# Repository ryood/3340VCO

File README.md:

# 3340VCO

AS3340/CEM3340を使用したアナログVCOです。

## 機能概要

電源入力 ±12V (Eurorack電源 10Pin)

### コントロール
FINE:  -0.5オクターブ～+0.5オクターブ連続可変

OCTAVE:  +0オクターブ～+4オクターブ切り替え

MOD:  モジュレーション・レベル

PWM:  PWMレベル調整 (PULSE_WIDTH設定値～PWM入力)

PULSE_WIDTH:  パルス幅調整

### 入出力
CV_IN:  CV入力

MOD_IN:  モジュレーション入力

PWM_IN:  PWM入力

OUT:  音声出力

入力信号電圧: -5V～+5V　出力信号振幅: -4V～+4V 

## 参考記事
[音源とオーディオの電子工作（予定）：3340VCO](https://dad8893.blogspot.com/search/label/3340VCO)

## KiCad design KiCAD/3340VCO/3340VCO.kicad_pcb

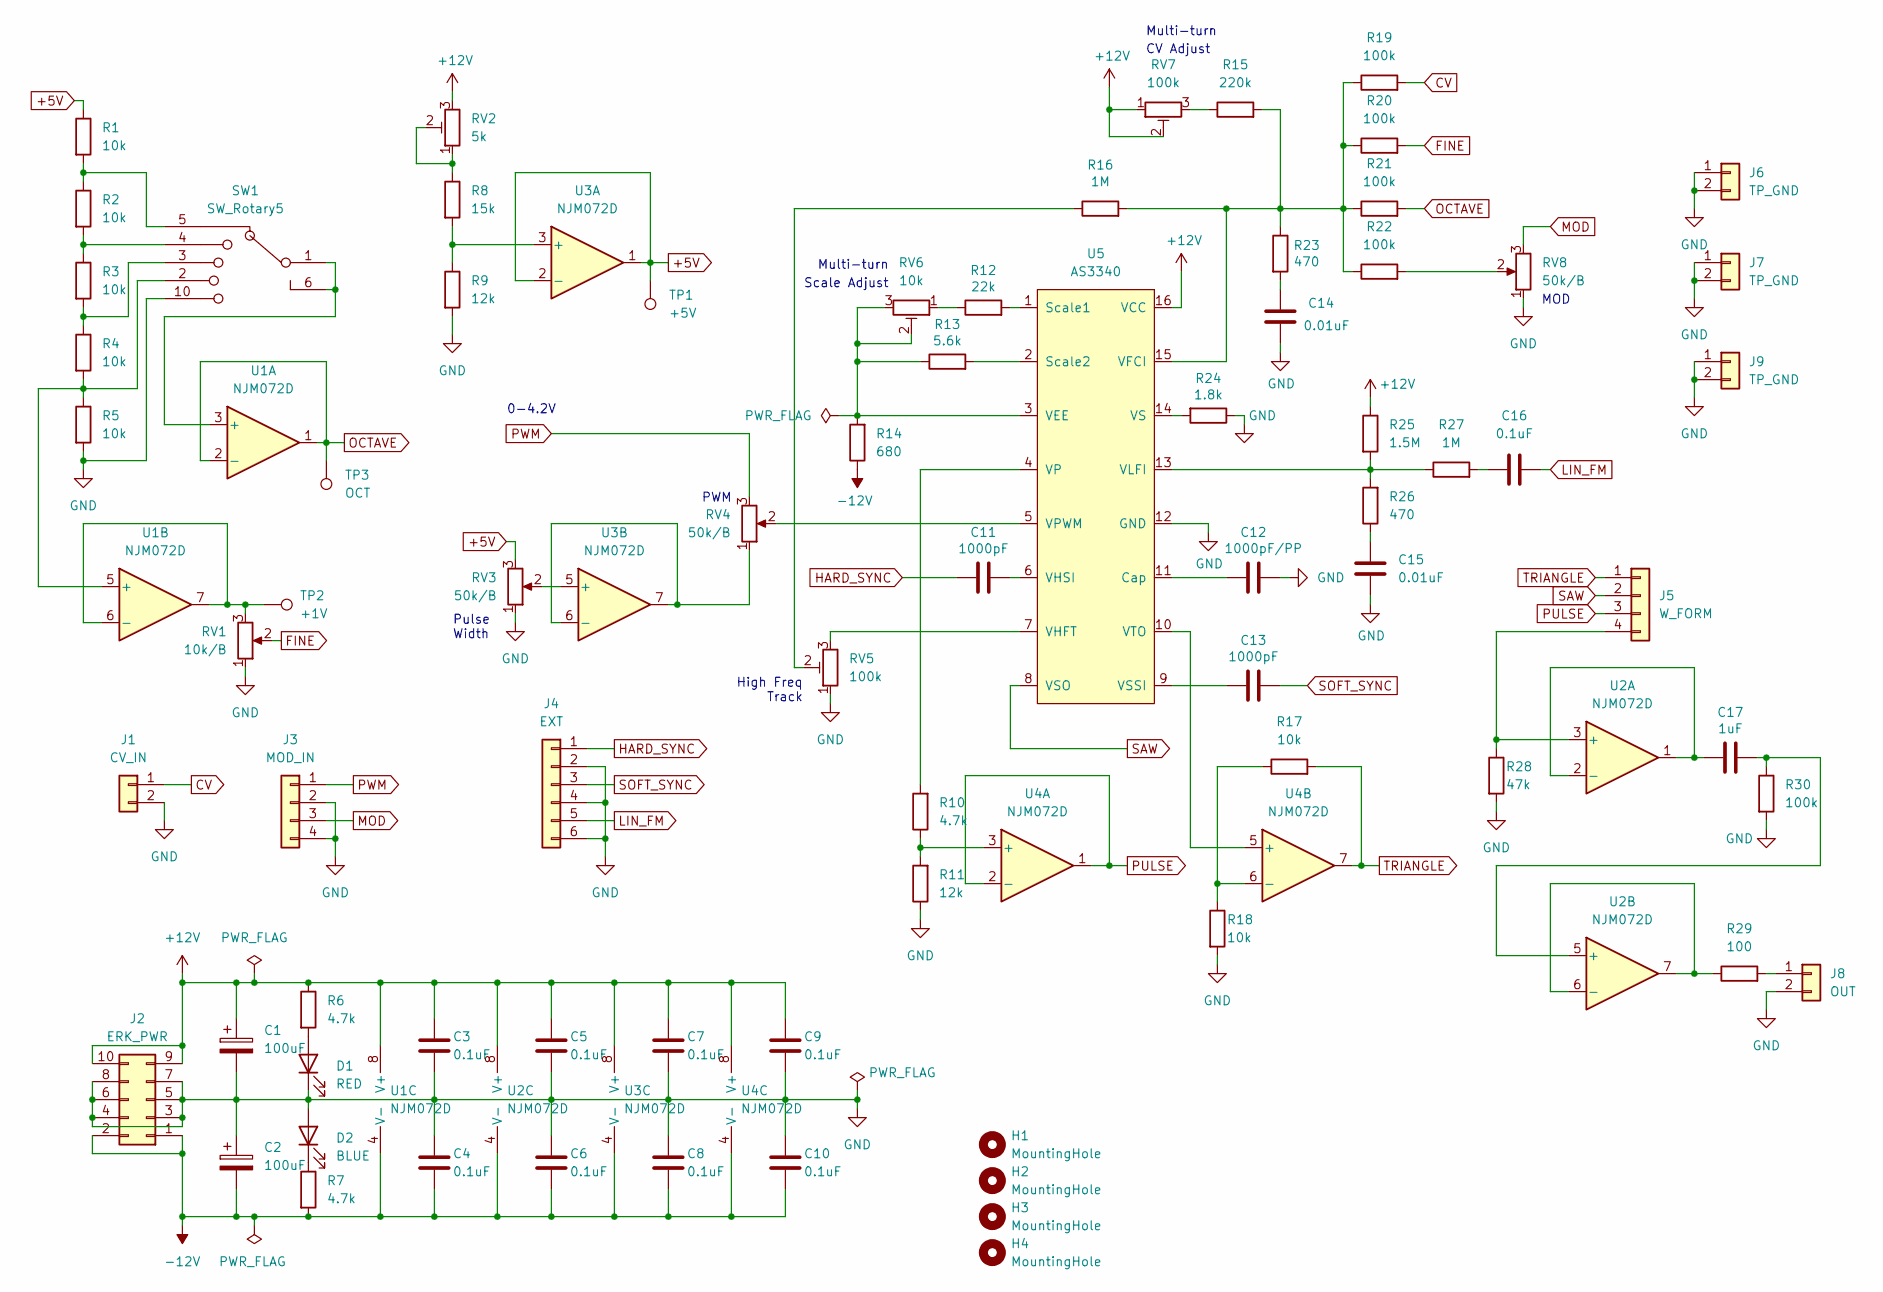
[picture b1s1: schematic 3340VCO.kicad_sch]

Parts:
C1, C2: 100uF; CP_Radial_D6.3mm_P2.50mm
C3, C4, C5, C6, C7, C8, C9, C10: 0.1uF; C_Disc_D3.0mm_W1.6mm_P2.50mm
C11, C13: 1000pF; C_Rect_L7.0mm_W2.0mm_P5.00mm
C12: 1000pF/PP; C_Rect_L7.0mm_W2.0mm_P5.00mm
C14, C15: 0.01uF; C_Rect_L7.0mm_W3.5mm_P5.00mm
C16: 0.1uF; C_Rect_L7.0mm_W3.5mm_P5.00mm
C17: 1uF; C_Rect_L7.0mm_W6.0mm_P5.00mm
D1: RED; LED_D3.0mm
D2: BLUE; LED_D3.0mm
H1, H2, H3, H4: MountingHole; MountingHole_3.2mm_M3
J1: CV_IN; JST_XH_B2B-XH-A_1x02_P2.50mm_Vertical
J2: ERK_PWR; IDC-Header_2x05_P2.54mm_Vertical
J3: MOD_IN; JST_XH_B4B-XH-A_1x04_P2.50mm_Vertical
J4: EXT; JST_XH_B6B-XH-A_1x06_P2.50mm_Vertical
J5: W_FORM; JST_XH_B4B-XH-A_1x04_P2.50mm_Vertical
J6, J7, J9: TP_GND; PinHeader_1x02_P2.54mm_Vertical
J8: OUT; JST_XH_B2B-XH-A_1x02_P2.50mm_Vertical
R1, R2, R3, R4, R5, R17, R18: 10k; R_Axial_DIN0207_L6.3mm_D2.5mm_P10.16mm_Horizontal
R6, R7, R10: 4.7k; R_Axial_DIN0207_L6.3mm_D2.5mm_P10.16mm_Horizontal
R8: 15k; R_Axial_DIN0207_L6.3mm_D2.5mm_P10.16mm_Horizontal
R9, R11: 12k; R_Axial_DIN0207_L6.3mm_D2.5mm_P10.16mm_Horizontal
R12: 22k; R_Axial_DIN0207_L6.3mm_D2.5mm_P10.16mm_Horizontal
R13: 5.6k; R_Axial_DIN0207_L6.3mm_D2.5mm_P10.16mm_Horizontal
R14: 680; R_Axial_DIN0207_L6.3mm_D2.5mm_P10.16mm_Horizontal
R15: 220k; R_Axial_DIN0207_L6.3mm_D2.5mm_P10.16mm_Horizontal
R16, R27: 1M; R_Axial_DIN0207_L6.3mm_D2.5mm_P10.16mm_Horizontal
R19, R20, R21, R22, R30: 100k; R_Axial_DIN0207_L6.3mm_D2.5mm_P10.16mm_Horizontal
R23, R26: 470; R_Axial_DIN0207_L6.3mm_D2.5mm_P10.16mm_Horizontal
R24: 1.8k; R_Axial_DIN0207_L6.3mm_D2.5mm_P10.16mm_Horizontal
R25: 1.5M; R_Axial_DIN0207_L6.3mm_D2.5mm_P10.16mm_Horizontal
R28: 47k; R_Axial_DIN0207_L6.3mm_D2.5mm_P10.16mm_Horizontal
R29: 100; R_Axial_DIN0207_L6.3mm_D2.5mm_P10.16mm_Horizontal
RV1: 10k/B; Potentiometer_Alps_RK09Y11_Single_Horizontal
RV2: 5k; Potentiometer_Bourns_3362P_Vertical
RV3, RV4, RV8: 50k/B; Potentiometer_Alps_RK09Y11_Single_Horizontal
RV5: 100k; Potentiometer_Bourns_3362P_Vertical
RV6: 10k; Potentiometer_Bourns_3296W_Vertical
RV7: 100k; Potentiometer_Bourns_3296W_Vertical
SW1: SW_Rotary5; Rotary_Ecoder_Ali_Jtom
TP1: +5V; TestPoint_Pad_D1.0mm
TP2: +1V; TestPoint_Pad_D1.0mm
TP3: OCT; TestPoint_Pad_D1.0mm
U1, U2, U3, U4: NJM072D; DIP-8_W7.62mm_Socket
U5: AS3340; DIP-16_W7.62mm_Socket

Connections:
+5V: R1.1, RV3.3, TP1.1, U3.1, U3.2 (-)
+12V: C1.1, C3.1, C5.1, C7.1, C9.1, J2.9, J2.10, R6.1, R25.1, RV2.3, RV7.1, RV7.2, U1.8 (V+), U2.8 (V+), U3.8 (V+), U4.8 (V+), U5.16 (VCC)
-12V: C2.2, C4.2, C6.2, C8.2, C10.2, J2.1, J2.2, R7.2, R14.1, U1.4 (V-), U2.4 (V-), U3.4 (V-), U4.4 (V-)
CV: J1.1, R19.2
FINE: R20.2, RV1.2
GND: C1.2, C2.1, C3.2, C4.1, C5.2, C6.1, C7.2, C8.1, C9.2, C10.1, C12.1, C14.2, C15.1, D1.1 (K), D2.2 (A), J1.2, J2.3, J2.4, J2.5, J2.6, J2.7, J2.8, J3.2, J3.4, J4.2, J4.4, J4.6, J6.1, J6.2, J7.1, J7.2, J8.2, J9.1, J9.2, R5.2, R9.2, R11.1, R18.2, R24.1, R28.2, R30.2, RV1.1, RV3.1, RV5.1, RV8.1, SW1.10, U5.12 (GND)
HARD_SYNC: C11.2, J4.1
LIN_FM: C16.2, J4.5
MOD: J3.3, RV8.3
unnamed: C11.1, U5.6 (VHSI)
unnamed: C12.2, U5.11 (Cap)
unnamed: C13.2, U5.9 (VSSI)
unnamed: C14.1, R23.2
unnamed: C15.2, R26.1
unnamed: C16.1, R27.2
unnamed: C17.1, R30.1, U2.5 (+)
unnamed: C17.2, U2.1, U2.2 (-)
unnamed: D1.2 (A), R6.2
unnamed: D2.1 (K), R7.1
unnamed: J5.4, R28.1, U2.3 (+)
unnamed: J8.1, R29.2
unnamed: R1.2, R2.1, SW1.5
unnamed: R2.2, R3.1, SW1.4
unnamed: R3.2, R4.1, SW1.3
unnamed: R4.2, R5.1, SW1.2, U1.5 (+)
unnamed: R8.1, RV2.1, RV2.2
unnamed: R8.2, R9.1, U3.3 (+)
unnamed: R10.1, R11.2, U4.3 (+)
unnamed: R10.2, U5.4 (VP)
unnamed: R12.1, RV6.1
unnamed: R12.2, U5.1 (Scale1)
unnamed: R13.1, R14.2, RV6.2, RV6.3, U5.3 (VEE)
unnamed: R13.2, U5.2 (Scale2)
unnamed: R15.1, RV7.3
unnamed: R15.2, R16.2, R19.1, R20.1, R21.1, R22.1, R23.1, U5.15 (VFCI)
unnamed: R16.1, RV5.2
unnamed: R17.1, R18.1, U4.6 (-)
unnamed: R22.2, RV8.2
unnamed: R24.2, U5.14 (VS)
unnamed: R25.2, R26.2, R27.1, U5.13 (VLFI)
unnamed: R29.1, U2.6 (-), U2.7
unnamed: RV1.3, TP2.1, U1.6 (-), U1.7
unnamed: RV3.2, U3.5 (+)
unnamed: RV4.1, U3.6 (-), U3.7
unnamed: RV4.2, U5.5 (VPWM)
unnamed: RV5.3, U5.7 (VHFT)
unnamed: SW1.1, SW1.6, U1.3 (+)
unnamed: U4.5 (+), U5.10 (VTO)
OCTAVE: R21.2, TP3.1, U1.1, U1.2 (-)
PULSE: J5.3, U4.1, U4.2 (-)
PWM: J3.1, RV4.3
SAW: J5.2, U5.8 (VSO)
SOFT_SYNC: C13.1, J4.3
TRIANGLE: J5.1, R17.2, U4.7

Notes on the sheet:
Multi-turn
0-4.2V
MOD
CV Adjust
Scale Adjust
High Freq Track
PWM
Pulse Width

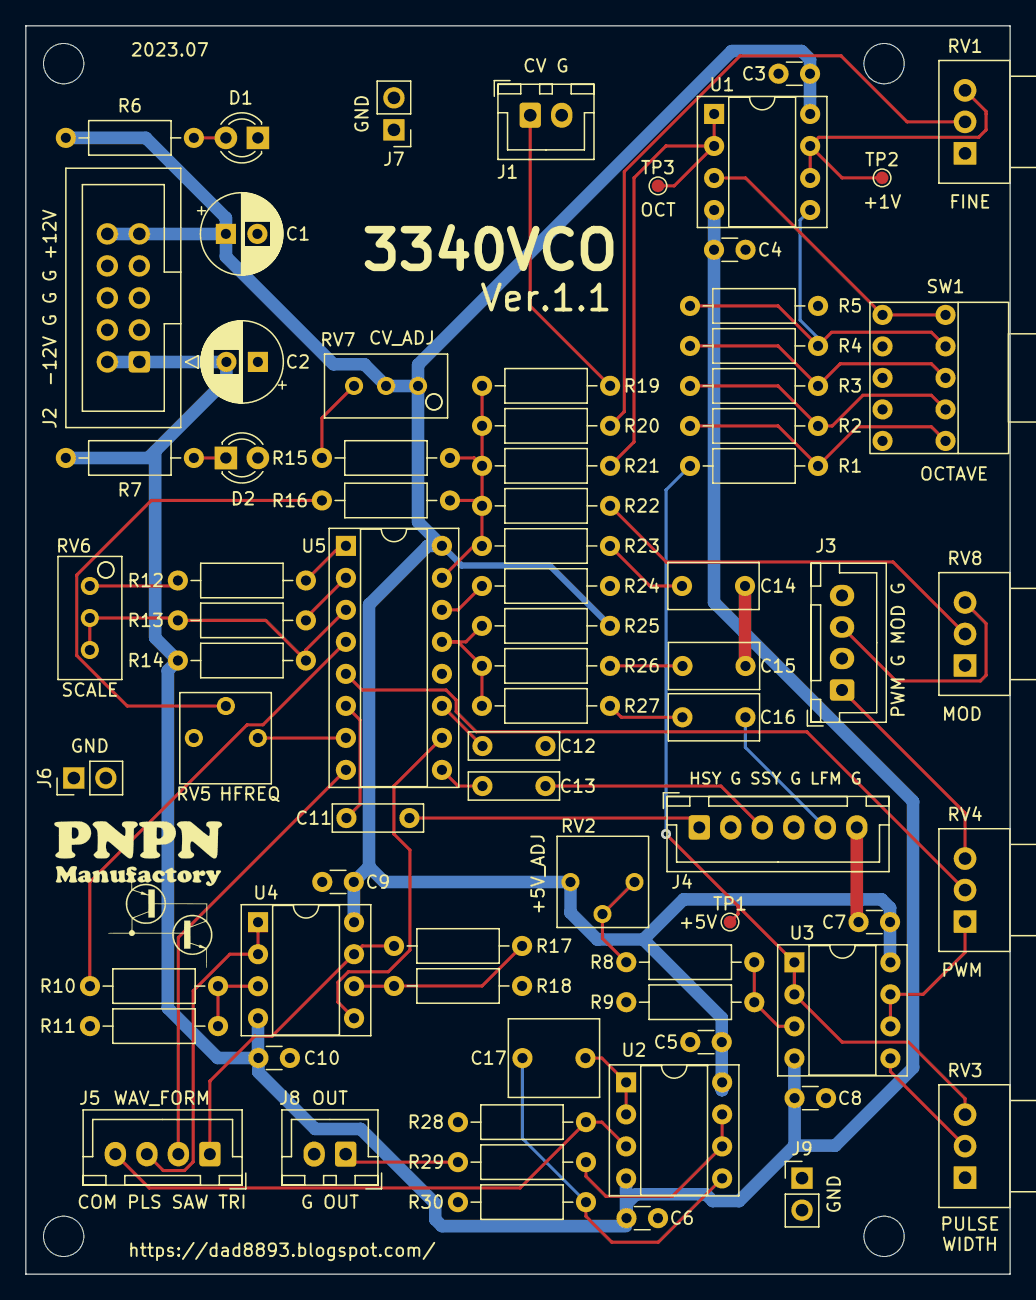
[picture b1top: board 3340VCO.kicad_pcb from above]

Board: 2 copper layers, 78.1 x 99.1 mm, 79 parts (0 on the bottom side), 54 nets.

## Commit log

2023-07-17 部品配置
2023-07-27 基板製造
2023-08-14 '23夏コミケ
2023-08-25 EXT Panel
2023-11-07 マニュアルを追加
